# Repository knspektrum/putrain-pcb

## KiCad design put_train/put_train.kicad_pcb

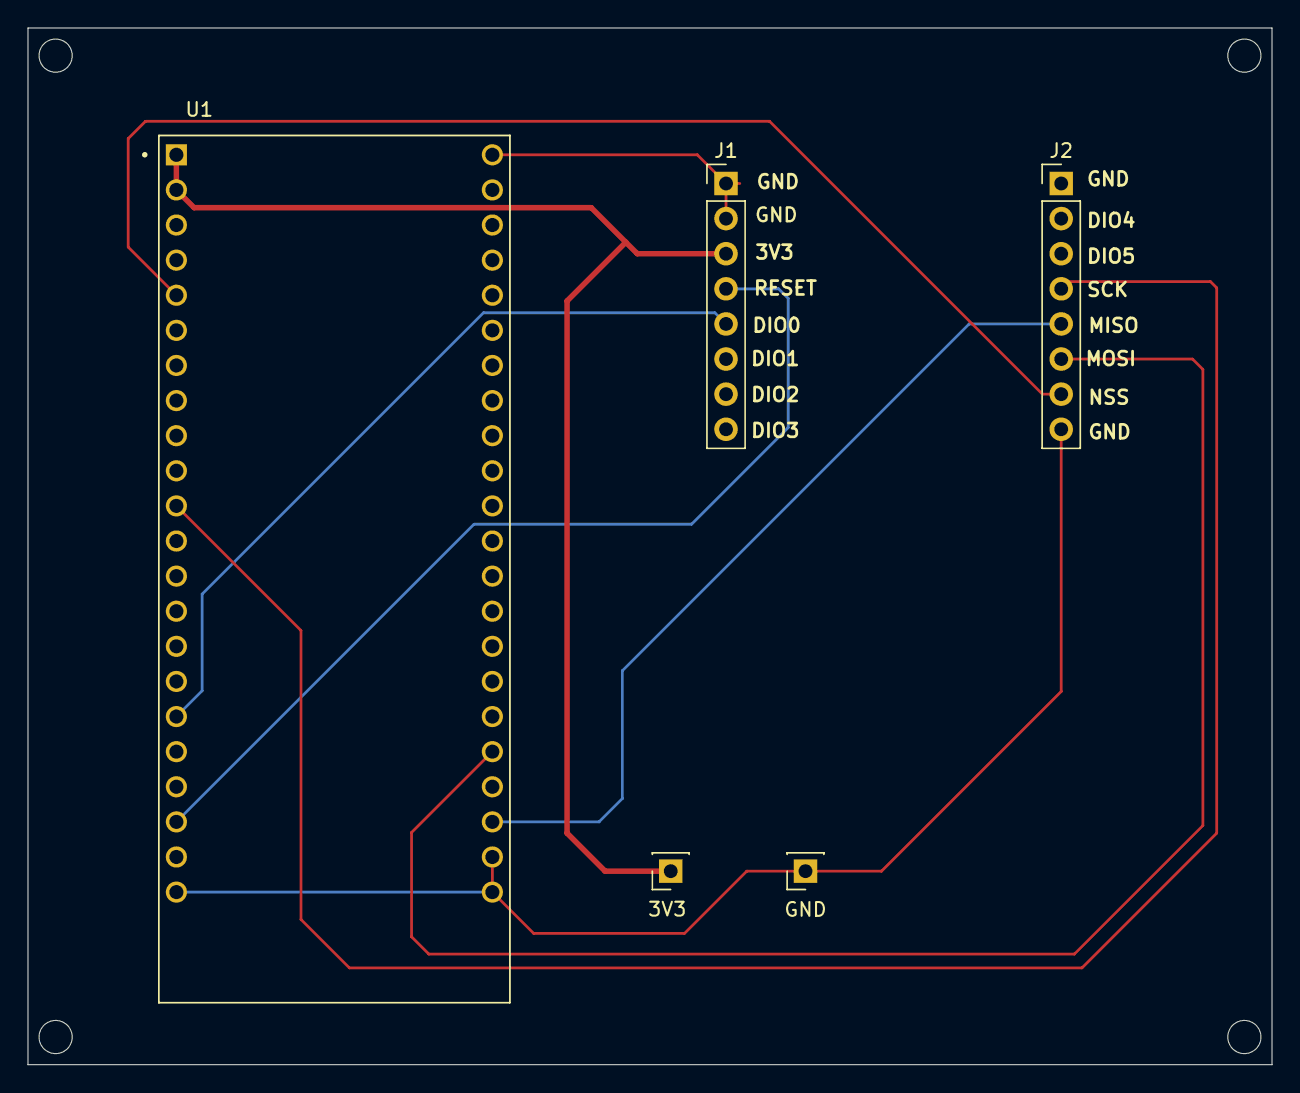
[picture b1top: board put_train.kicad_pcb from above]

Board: 2 copper layers, 90.0 x 75.0 mm, 5 parts (0 on the bottom side), 8 nets.

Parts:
GND: Conn_01x01_Socket; PinSocket_1x01_P2.54mm_Vertical
J1, J2: Conn_01x08_Pin; PinHeader_1x08_P2.54mm_Vertical
J3: Conn_01x01_Socket; PinSocket_1x01_P2.54mm_Vertical
U1: ESP32-S3-DEVKITC-1-N8R8

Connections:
/3V3: J1.3 (3V3), J3.1 (Pin_1_1), U1.J1_1 (3V3), U1.J1_2 (3V3.)
unnamed: J1.5 (DIO0), U1.J1_17 (GPIO11)
unnamed: J1.4 (RESET), U1.J1_20 (GPIO14)
unnamed: J2.5 (MISO), U1.J3_20 (USB_D-/GPIO19)
unnamed: J2.6 (MOSI), U1.J3_18 (GPIO21)
unnamed: J2.7 (NSS), U1.J1_5 (GPIO5)
unnamed: J2.4 (SCK), U1.J1_11 (GPIO18)
unnamed: GND.1 (Pin_1_1), J1.1 (GND), J1.2 (GND), J2.8 (GND), U1.J1_22 (GND3), U1.J3_1 (GND), U1.J3_21 (GND1), U1.J3_22 (GND2)

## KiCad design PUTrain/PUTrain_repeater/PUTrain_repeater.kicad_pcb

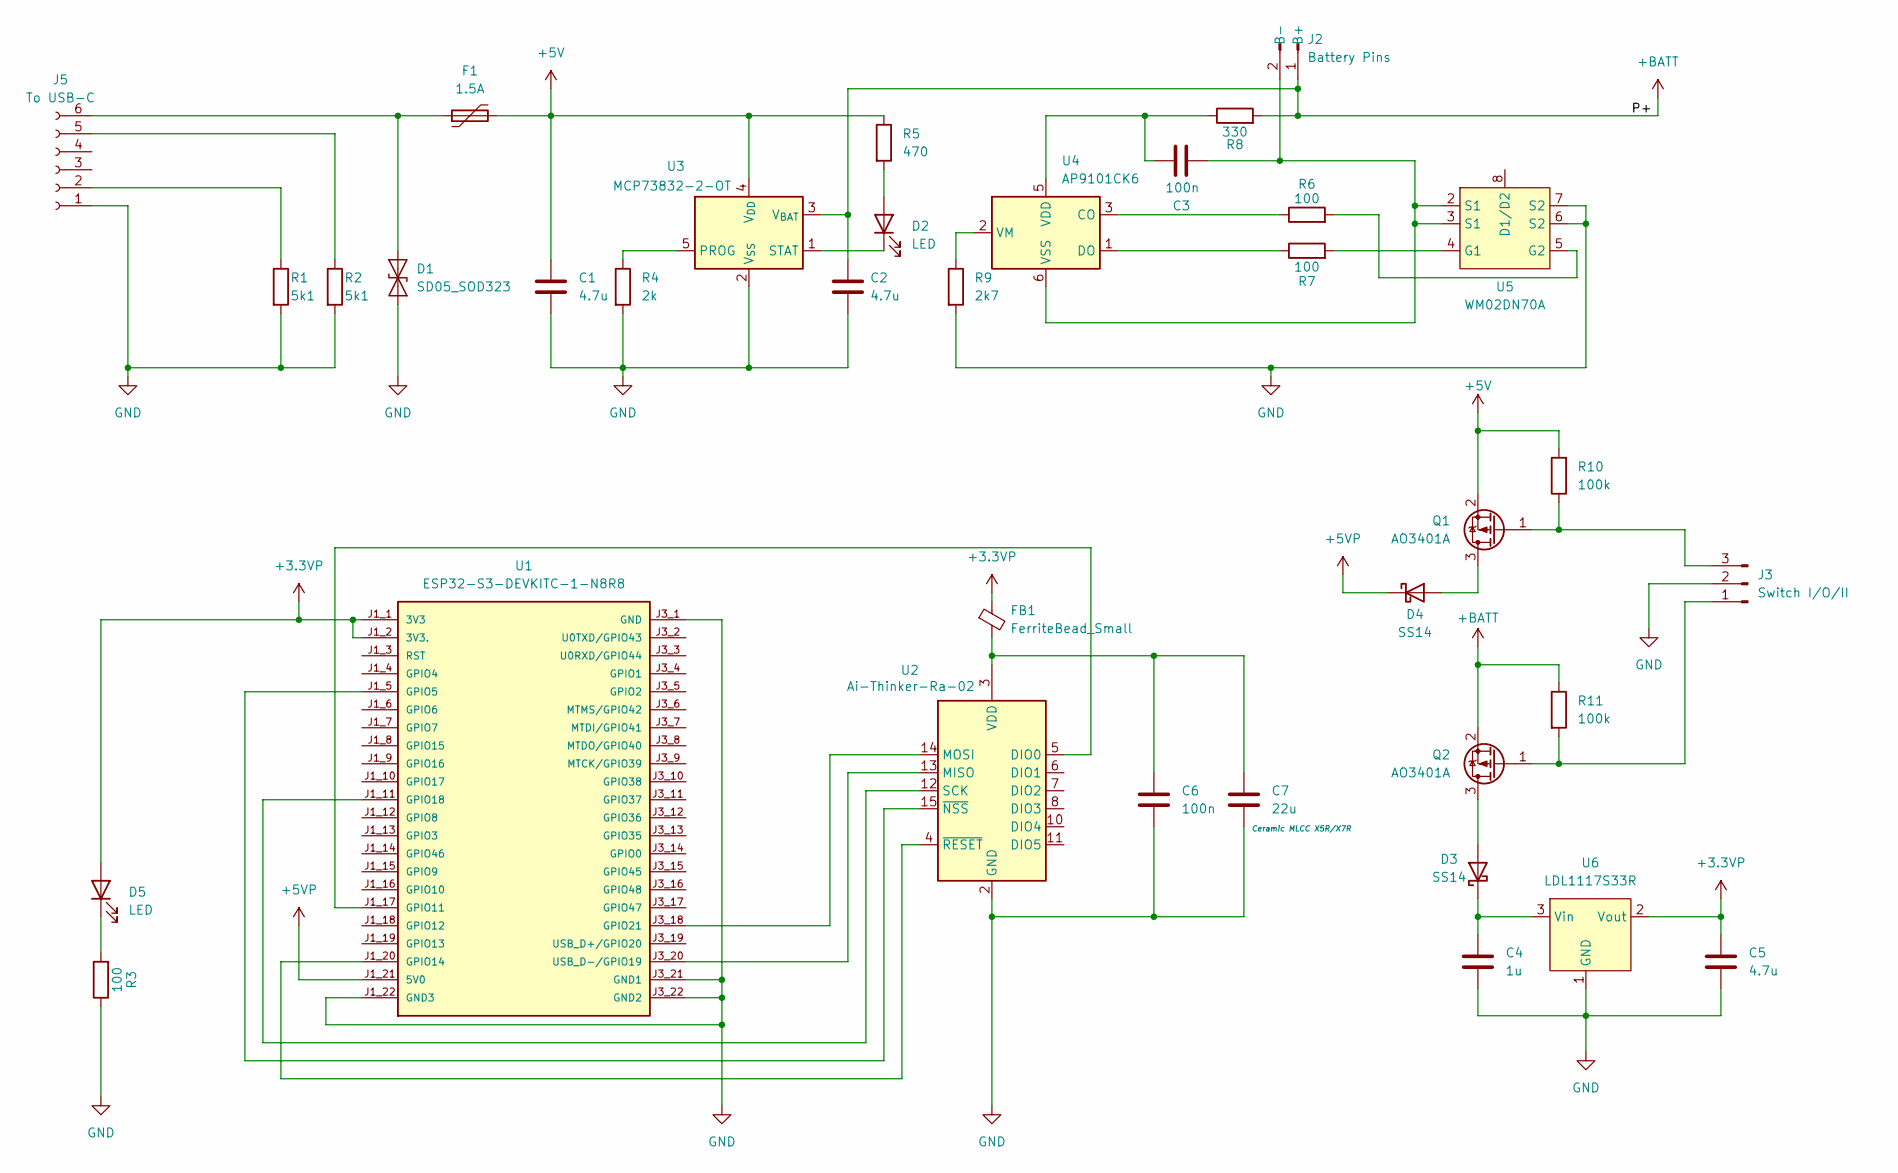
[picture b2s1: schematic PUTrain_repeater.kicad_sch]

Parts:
C1, C2, C5: 4.7u; C_1206_3216Metric_Pad1.33x1.80mm_HandSolder
C3, C6: 100n; C_0805_2012Metric_Pad1.18x1.45mm_HandSolder
C4: 1u; C_0805_2012Metric_Pad1.18x1.45mm_HandSolder
C7: 22u; C_1210_3225Metric_Pad1.33x2.70mm_HandSolder
D1: SD05_SOD323; D_SOD-323
D2, D5: LED; LED_D1.8mm_W1.8mm_H2.4mm_Horizontal_O1.27mm_Z8.2mm
D3, D4: SS14; D_SMA
F1: 1.5A; Fuse_1812_4532Metric_Pad1.30x3.40mm_HandSolder
FB1: FerriteBead_Small; C_0603_1608Metric_Pad1.08x0.95mm_HandSolder
J2: Battery Pins; SolderWire-0.75sqmm_1x02_P4.8mm_D1.25mm_OD2.3mm
J3: Switch I/O/II; SolderWire-0.75sqmm_1x03_P4.8mm_D1.25mm_OD2.3mm
J5: To USB-C; JST_PH_B6B-PH-K_1x06_P2.00mm_Vertical
Q1, Q2: AO3401A; SOT-23
R1, R2: 5k1; R_0603_1608Metric_Pad0.98x0.95mm_HandSolder
R3, R6, R7: 100; R_0805_2012Metric_Pad1.20x1.40mm_HandSolder
R4: 2k; R_0805_2012Metric_Pad1.20x1.40mm_HandSolder
R5: 470; R_0805_2012Metric_Pad1.20x1.40mm_HandSolder
R8: 330; R_0805_2012Metric_Pad1.20x1.40mm_HandSolder
R9: 2k7; R_0603_1608Metric_Pad0.98x0.95mm_HandSolder
R10, R11: 100k; R_0805_2012Metric_Pad1.20x1.40mm_HandSolder
U1: ESP32-S3-DEVKITC-1-N8R8
U2: Ai-Thinker-Ra-02; Ai-Thinker-Ra-01-LoRa
U3: MCP73832-2-OT; SOT-23-5
U4: AP9101CK6; SOT-23-6
U5: WM02DN70A; TSSOP-8_4.4x3mm_P0.65mm
U6: LDL1117S33R; SOT-223

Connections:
+3.3VP: C5.1, D5.2 (A), FB1.1, U1.J1_1 (3V3), U1.J1_2 (3V3.), U6.2 (Vout), U6.4 (Vout)
+5V: C1.1, F1.2, Q1.2 (S), R5.1, R10.2, U3.4 (V_{DD})
+5VP: D4.1 (K), U1.J1_21 (5V0)
+BATT: C2.1, J2.1 (B+), Q2.2 (S), R8.2, R11.1, U3.3 (V_{BAT})
GND: C1.2, C2.2, C4.2, C5.2, C6.2, C7.2, D1.1 (A1), J3.2, J5.1, R1.2, R2.2, R3.1, R4.2, R9.2, U1.J1_22 (GND3), U1.J3_1 (GND), U1.J3_21 (GND1), U1.J3_22 (GND2), U2.1 (GND), U2.2 (GND), U2.9 (GND), U2.16 (GND), U3.2 (V_{SS}), U5.6 (S2), U5.7 (S2), U6.1 (GND)
unnamed: D1.2 (A2), F1.1, J5.6
unnamed: D2.2 (A), R5.2
unnamed: D2.1 (K), U3.1 (STAT)
unnamed: D3.2 (A), Q2.3 (D)
unnamed: C4.1, D3.1 (K), U6.3 (Vin)
unnamed: D4.2 (A), Q1.3 (D)
unnamed: D5.1 (K), R3.2
unnamed: C3.1, J2.2 (B-), U4.6 (VSS), U5.2 (S1), U5.3 (S1)
unnamed: J3.1, Q2.1 (G), R11.2
unnamed: J3.3, Q1.1 (G), R10.1
unnamed: J5.2, R1.1
unnamed: J5.5, R2.1
unnamed: U1.J1_5 (GPIO5), U2.15 (~NSS)
unnamed: U1.J1_17 (GPIO11), U2.5 (DIO0)
unnamed: U1.J1_20 (GPIO14), U2.4 (~RESET)
unnamed: U1.J1_11 (GPIO18), U2.12 (SCK)
unnamed: U1.J3_18 (GPIO21), U2.14 (MOSI)
unnamed: U1.J3_20 (USB_D-/GPIO19), U2.13 (MISO)
unnamed: C6.1, C7.1, FB1.2, U2.3 (VDD)
unnamed: R4.1, U3.5 (PROG)
unnamed: R6.1, U4.3 (CO)
unnamed: R7.1, U4.1 (DO)
unnamed: C3.2, R8.1, U4.5 (VDD)
unnamed: R9.1, U4.2 (VM)
unnamed: U5.1 (D1/D2), U5.8 (D1/D2)
unnamed: R7.2, U5.4 (G1)
unnamed: R6.2, U5.5 (G2)

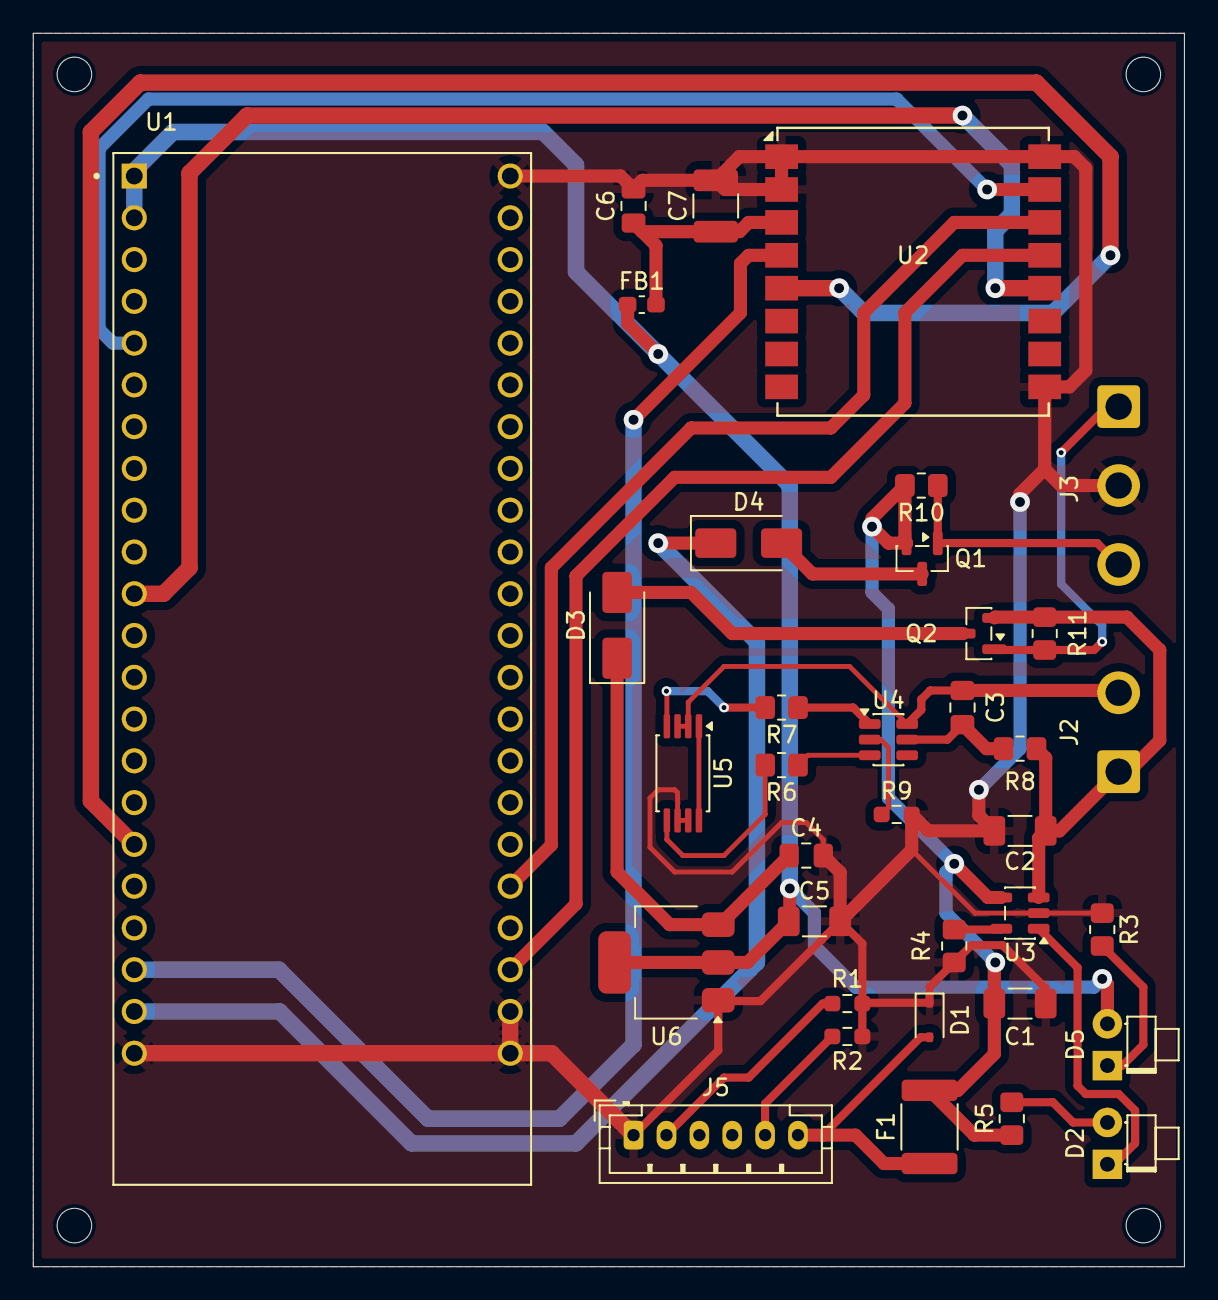
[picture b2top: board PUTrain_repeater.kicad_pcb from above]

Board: 2 copper layers, 70.0 x 75.0 mm, 36 parts (0 on the bottom side), 32 nets.

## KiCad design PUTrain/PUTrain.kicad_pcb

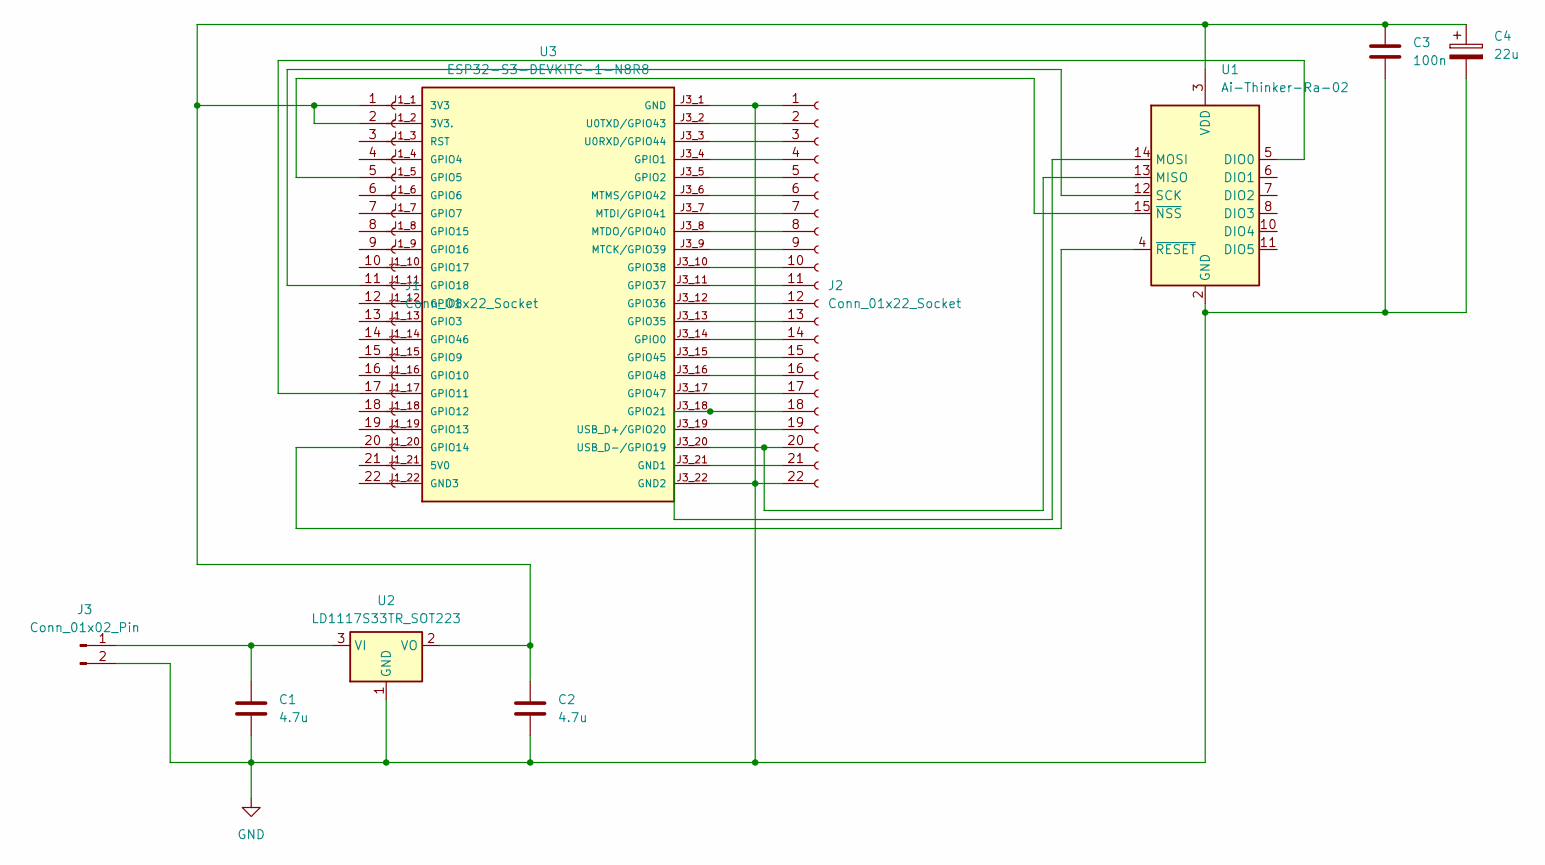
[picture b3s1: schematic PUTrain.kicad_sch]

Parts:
C1, C2: 4.7u; C_0805_2012Metric
C3: 100n; C_0402_1005Metric
C4: 22u; C_1206_3216Metric
J1, J2: Conn_01x22_Socket; PinSocket_1x22_P2.54mm_Vertical
J3: Conn_01x02_Pin; PhoenixContact_MSTBA_2,5_2-G_1x02_P5.00mm_Horizontal
U1: Ai-Thinker-Ra-02; Ai-Thinker-Ra-01-LoRa
U2: LD1117S33TR_SOT223; SOT-223-3_TabPin2
U3: ESP32-S3-DEVKITC-1-N8R8

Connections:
GND: C1.2, C2.2, C3.2, C4.2, J2.1, J2.21, J2.22, J3.2, U1.1 (GND), U1.2 (GND), U1.9 (GND), U1.16 (GND), U2.1 (GND), U3.J3_1 (GND), U3.J3_21 (GND1), U3.J3_22 (GND2)
unnamed: C2.1, C3.1, C4.1, J1.1, J1.2, U1.3 (VDD), U2.2 (VO)
unnamed: J1.5, U1.15 (~NSS)
unnamed: J1.11, U1.12 (SCK)
unnamed: J1.17, U1.5 (DIO0)
unnamed: J1.20, U1.4 (~RESET)
unnamed: J2.18, U1.14 (MOSI), U3.J3_18 (GPIO21)
unnamed: J2.20, U1.13 (MISO), U3.J3_20 (USB_D-/GPIO19)
unnamed: C1.1, J3.1, U2.3 (VI)
unnamed: J2.2, U3.J3_2 (U0TXD/GPIO43)
unnamed: J2.3, U3.J3_3 (U0RXD/GPIO44)
unnamed: J2.4, U3.J3_4 (GPIO1)
unnamed: J2.5, U3.J3_5 (GPIO2)
unnamed: J2.6, U3.J3_6 (MTMS/GPIO42)
unnamed: J2.7, U3.J3_7 (MTDI/GPIO41)
unnamed: J2.8, U3.J3_8 (MTDO/GPIO40)
unnamed: J2.9, U3.J3_9 (MTCK/GPIO39)
unnamed: J2.10, U3.J3_10 (GPIO38)
unnamed: J2.11, U3.J3_11 (GPIO37)
unnamed: J2.12, U3.J3_12 (GPIO36)
unnamed: J2.13, U3.J3_13 (GPIO35)
unnamed: J2.14, U3.J3_14 (GPIO0)
unnamed: J2.15, U3.J3_15 (GPIO45)
unnamed: J2.16, U3.J3_16 (GPIO48)
unnamed: J2.17, U3.J3_17 (GPIO47)
unnamed: J2.19, U3.J3_19 (USB_D+/GPIO20)

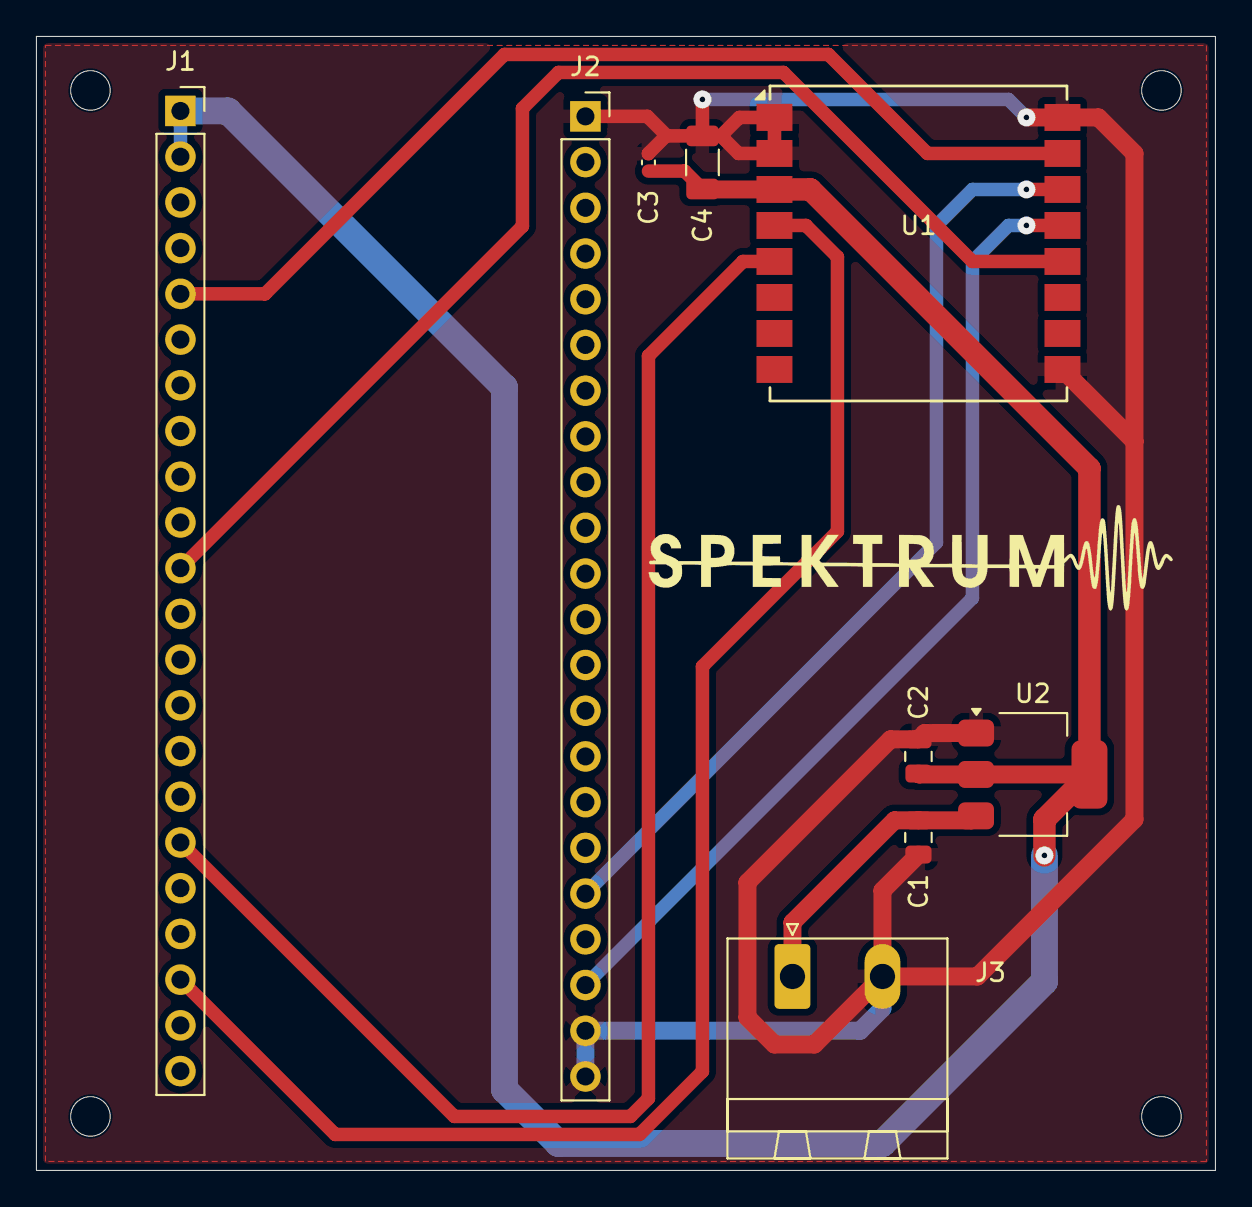
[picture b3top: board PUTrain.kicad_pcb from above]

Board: 2 copper layers, 65.5 x 63.0 mm, 9 parts (0 on the bottom side), 9 nets.

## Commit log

2026-03-31 Add files via upload
    płytka do przejrzenia oraz pewnie do poprawy
2026-03-31 Add library and PUTrain snapshot
2026-03-31 Add files via upload
    plytka do przejrzenia
2026-04-29 Add put_train snapshot
2026-05-26 Add Innowacja telemetry sketches
2026-05-26 Add Wireless_Telemetry overlay
2026-06-04 feat: make sender and reciever agnostic of input data
